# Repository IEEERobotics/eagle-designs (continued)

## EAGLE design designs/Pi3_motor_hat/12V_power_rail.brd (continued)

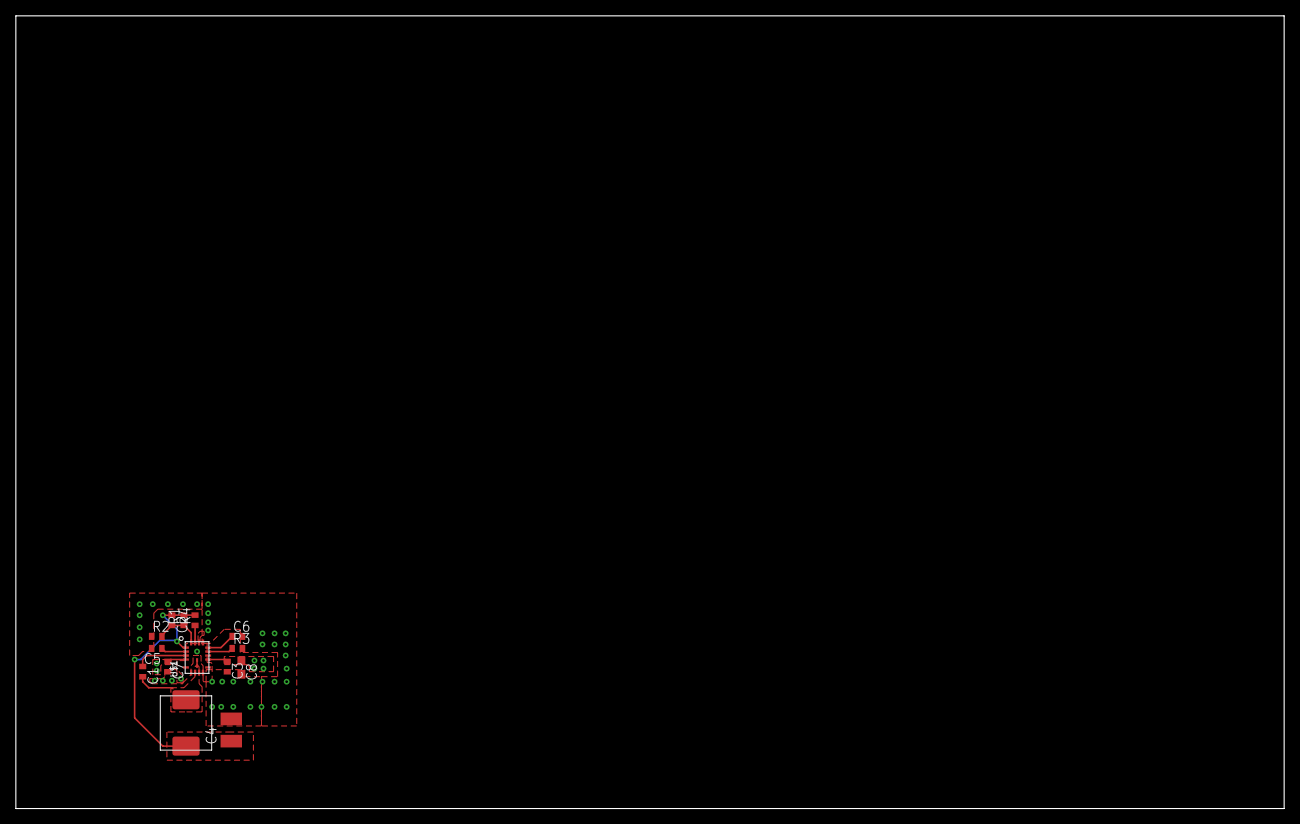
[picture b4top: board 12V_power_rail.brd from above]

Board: 2 copper layers, 160.0 x 100.0 mm, 14 parts (0 on the bottom side), 10 nets.

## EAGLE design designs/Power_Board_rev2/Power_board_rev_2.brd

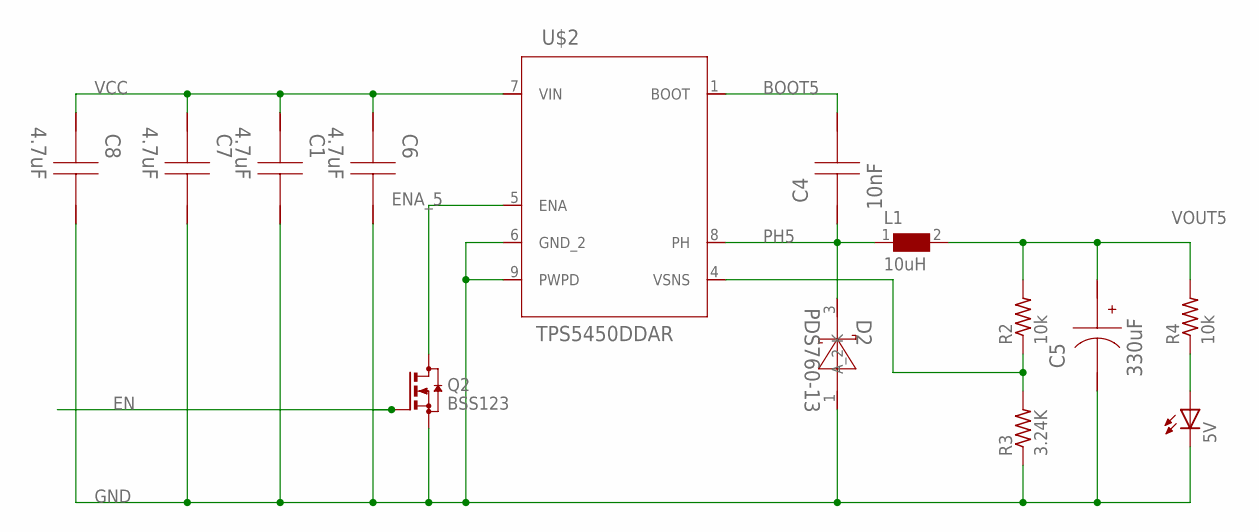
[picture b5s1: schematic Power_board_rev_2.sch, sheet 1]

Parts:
5V: LEDSML1206; SML1206
C1, C6, C7, C8: 4.7uF; 1206
C4: 10nF; 0805
C5: 330uF; SM_RADIAL_10AMM
D2: PDS760-13; POWERDI5
L1: 10uH; WE-HCC_1090
Q2: BSS123; SOT23
R2, R4: 10k; R1206
R3: 3.24K; R1206
U$2: TPS5450DDAR; R-PDSO-G8

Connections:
BOOT5: C4.1, U$2.1 (BOOT)
EN: Q2.1 (G); also elsewhere on the board
ENA_5: Q2.3 (D), U$2.5 (ENA)
FB5: 5V.A, R4.1
GND: 5V.C, C1.1, C5.2 (-), C6.1, C7.1, C8.1, D2.1 (A_2), Q2.2 (S), R3.1, U$2.6 (GND_2), U$2.9 (PWPD); also elsewhere on the board
PH5: C4.2, D2.3 (K), L1.1, U$2.8 (PH)
VCC: C1.2, C6.2, C7.2, C8.2, U$2.7 (VIN); also elsewhere on the board
VOUT5: C5.1 (+), L1.2, R2.2, R4.2; also elsewhere on the board
VSNS5: R2.1, R3.2, U$2.4 (VSNS)

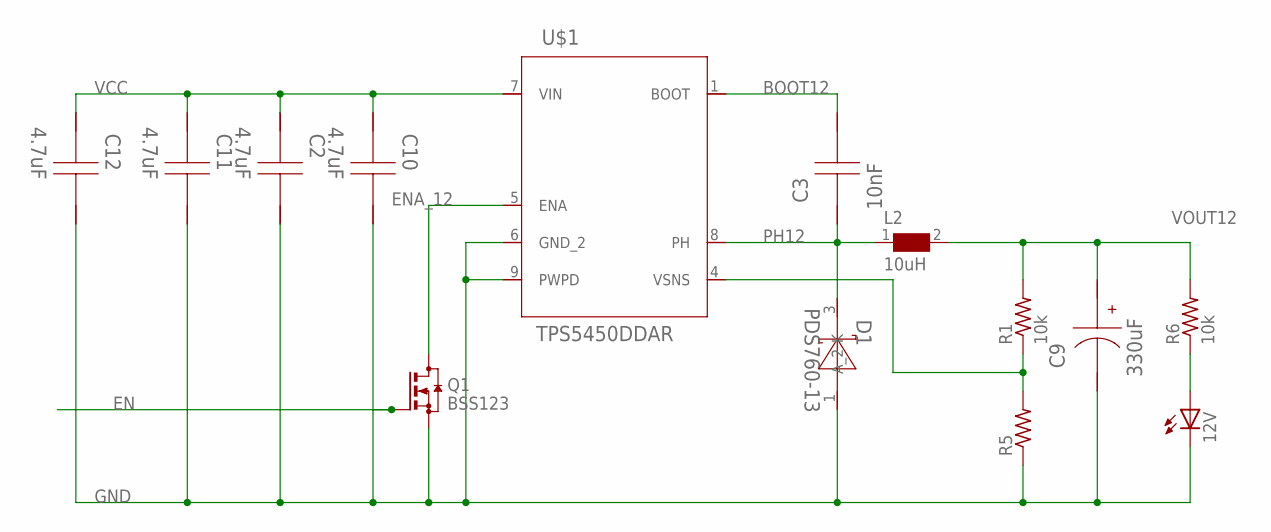
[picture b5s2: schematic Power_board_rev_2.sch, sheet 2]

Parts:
12V: LEDSML1206; SML1206
C2, C10, C11, C12: 4.7uF; 1206
C3: 10nF; 0805
C9: 330uF; SM_RADIAL_10AMM
D1: PDS760-13; POWERDI5
L2: 10uH; WE-HCC_1090
Q1: BSS123; SOT23
R1, R6: 10k; R1206
R5: R-US_R1206; R1206
U$1: TPS5450DDAR; R-PDSO-G8

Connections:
BOOT12: C3.1, U$1.1 (BOOT)
EN: Q1.1 (G); also elsewhere on the board
ENA_12: Q1.3 (D), U$1.5 (ENA)
FB12: 12V.A, R6.1
GND: 12V.C, C2.1, C9.2 (-), C10.1, C11.1, C12.1, D1.1 (A_2), Q1.2 (S), R5.1, U$1.6 (GND_2), U$1.9 (PWPD); also elsewhere on the board
PH12: C3.2, D1.3 (K), L2.1, U$1.8 (PH)
VCC: C2.2, C10.2, C11.2, C12.2, U$1.7 (VIN); also elsewhere on the board
VOUT12: C9.1 (+), L2.2, R1.2, R6.2; also elsewhere on the board
VSNS12: R1.1, R5.2, U$1.4 (VSNS)

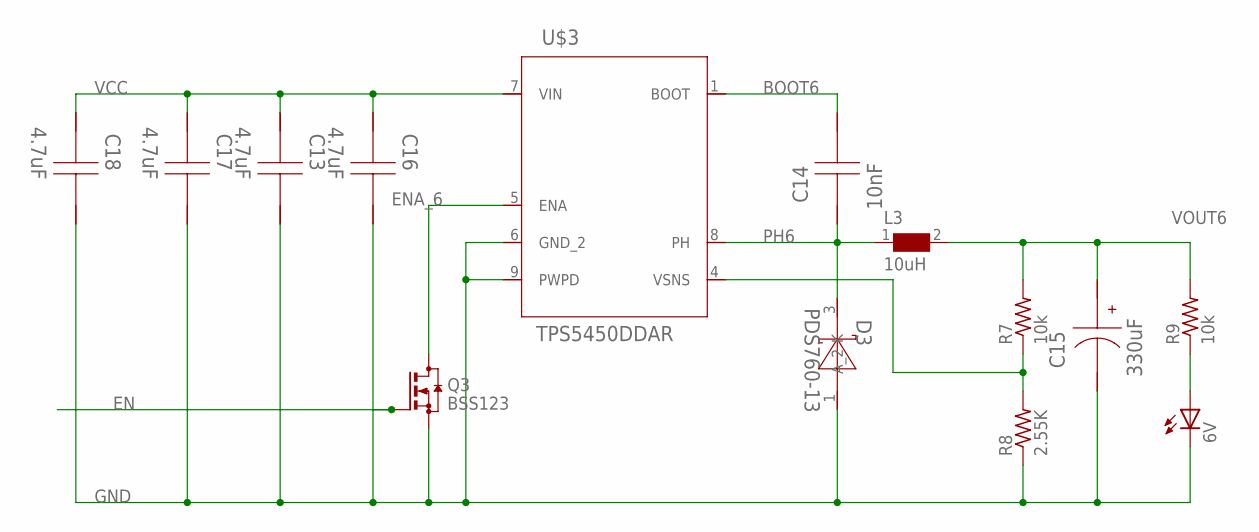
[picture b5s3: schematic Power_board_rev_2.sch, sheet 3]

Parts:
6V: LEDSML1206; SML1206
C13, C16, C17, C18: 4.7uF; 1206
C14: 10nF; 0805
C15: 330uF; SM_RADIAL_10AMM
D3: PDS760-13; POWERDI5
L3: 10uH; WE-HCC_1090
Q3: BSS123; SOT23
R7, R9: 10k; R1206
R8: 2.55K; R1206
U$3: TPS5450DDAR; R-PDSO-G8

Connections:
BOOT6: C14.1, U$3.1 (BOOT)
EN: Q3.1 (G); also elsewhere on the board
ENA_6: Q3.3 (D), U$3.5 (ENA)
FB6: 6V.A, R9.1
GND: 6V.C, C13.1, C15.2 (-), C16.1, C17.1, C18.1, D3.1 (A_2), Q3.2 (S), R8.1, U$3.6 (GND_2), U$3.9 (PWPD); also elsewhere on the board
PH6: C14.2, D3.3 (K), L3.1, U$3.8 (PH)
VCC: C13.2, C16.2, C17.2, C18.2, U$3.7 (VIN); also elsewhere on the board
VOUT6: C15.1 (+), L3.2, R7.2, R9.2; also elsewhere on the board
VSNS6: R7.1, R8.2, U$3.4 (VSNS)

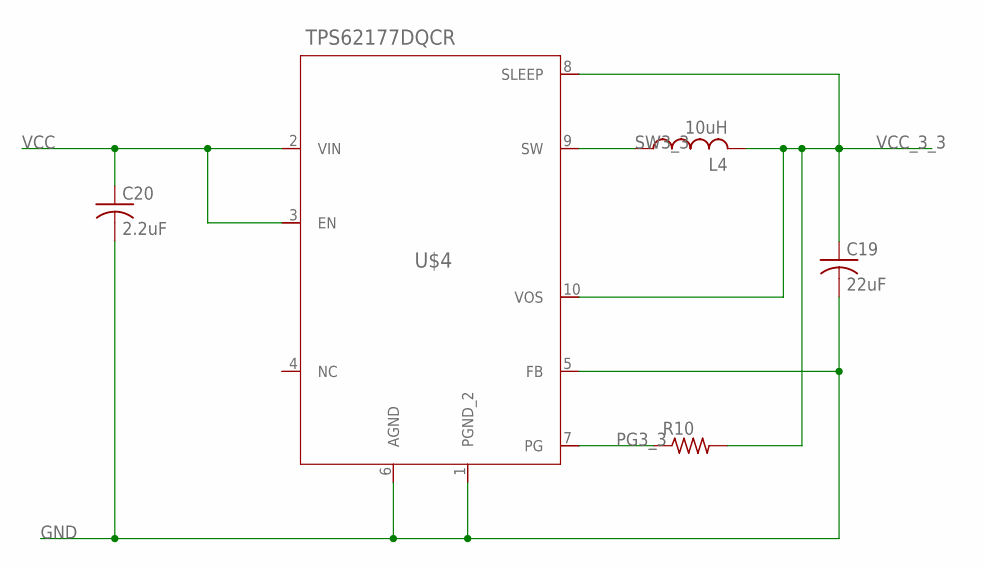
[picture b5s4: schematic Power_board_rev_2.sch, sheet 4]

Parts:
C19: 22uF; C0805
C20: 2.2uF; C1210K
L4: 10uH; POWER-CHOKE_WE-TPC
R10: R-US_R0402; R0402
U$4: TPS62177DQCR; R-PWSON-N10

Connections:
GND: C19.2, C20.2, U$4.1 (PGND_2), U$4.5 (FB), U$4.6 (AGND); also elsewhere on the board
PG3_3: R10.1, U$4.7 (PG)
SW3_3: L4.1, U$4.9 (SW)
VCC: C20.1, U$4.2 (VIN), U$4.3 (EN); also elsewhere on the board
VCC_3_3: C19.1, L4.2, R10.2, U$4.8 (SLEEP), U$4.10 (VOS); also elsewhere on the board

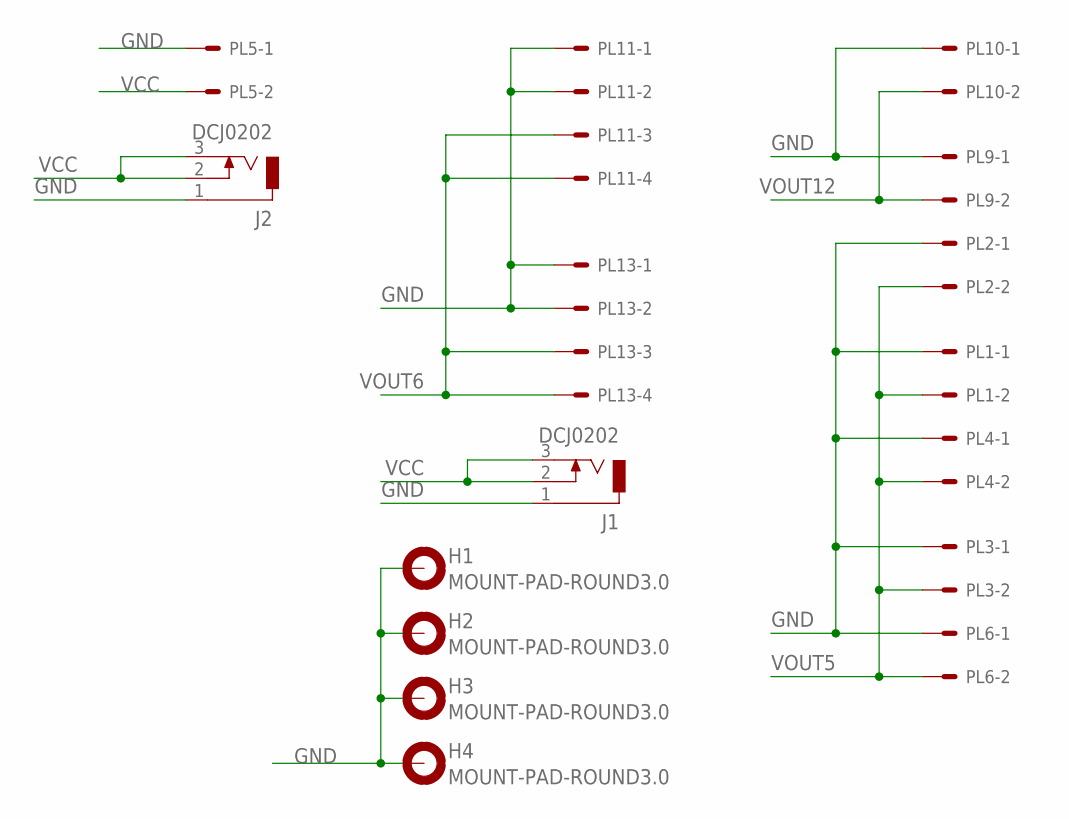
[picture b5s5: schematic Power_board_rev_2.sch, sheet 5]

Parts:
H1, H2, H3, H4: MOUNT-PAD-ROUND3.0; 3,0-PAD
J1, J2: DCJ0202
PL1, PL2, PL3, PL4, PL5, PL6, PL9, PL10: 555X-2H; 5569-2
PL11, PL13: 555X-4H; 5569-4

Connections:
GND: H1.B3,0, H2.B3,0, H3.B3,0, H4.B3,0, J1.1, J2.1, PL1.1, PL2.1, PL3.1, PL4.1, PL5.1, PL6.1, PL9.1, PL10.1, PL11.1, PL11.2, PL13.1, PL13.2; also elsewhere on the board
VCC: J1.2, J1.3, J2.2, J2.3, PL5.2; also elsewhere on the board
VOUT5: PL1.2, PL2.2, PL3.2, PL4.2, PL6.2; also elsewhere on the board
VOUT6: PL11.3, PL11.4, PL13.3, PL13.4; also elsewhere on the board
VOUT12: PL9.2, PL10.2; also elsewhere on the board

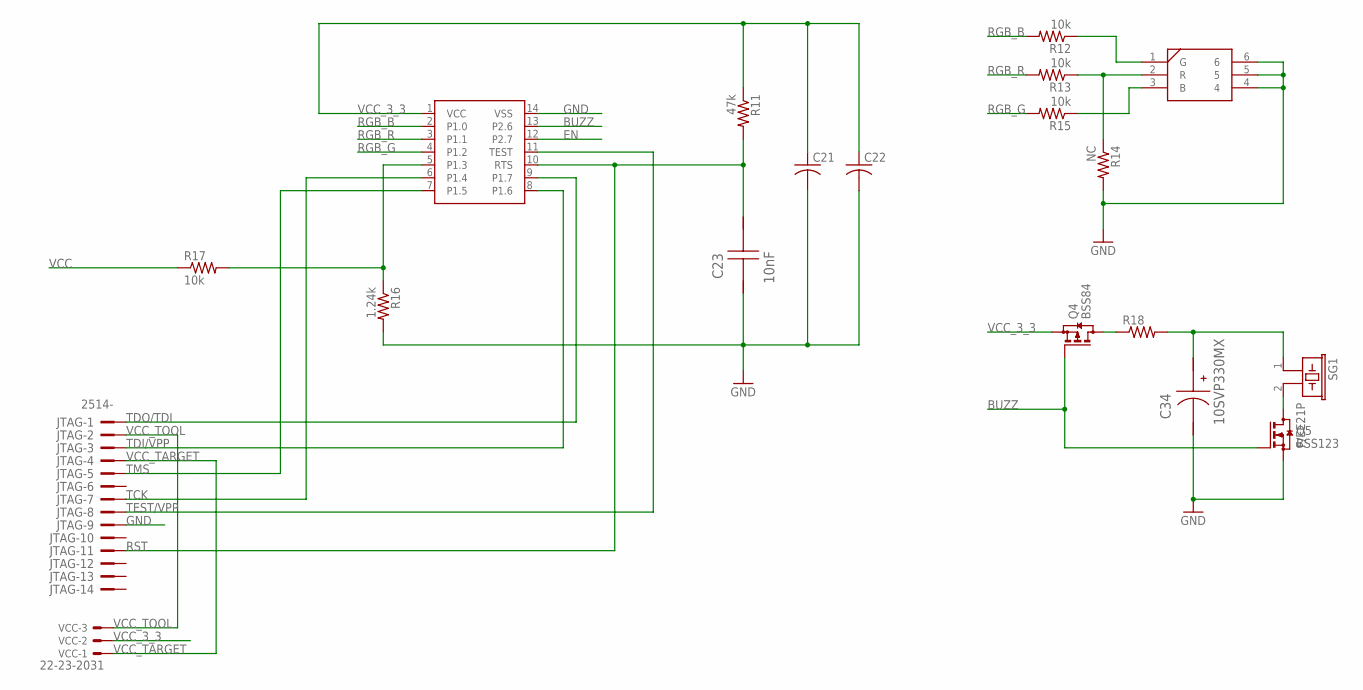
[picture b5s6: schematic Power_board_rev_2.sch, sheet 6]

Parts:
C21, C22: C-USC1206K; C1206K
C23: 10nF; 0805
C34: 10SVP330MX; SM_RADIAL_10AMM
JTAG: 2514-; PAK100/2500-14
Q4: BSS84; SOT23
Q5: BSS123; SOT23
R11: 47k; R1206W
R12, R13, R15, R17: 10k; R1206W
R14: NC; R1206W
R16: 1.24k; R1206W
R18: R-US_R1206W; R1206W
SG1: F/EE21P
U$5: MSP430F20X3; TSSOP-14
U$7: RGB; RGB_SMD
VCC: 22-23-2031

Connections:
BUZZ: Q4.1 (G), Q5.1 (G), U$5.13 (P2.6)
EN: U$5.12 (P2.7); also elsewhere on the board
GND: C21.2, C22.2, C23.2, C34.2 (-), JTAG.9, Q5.2 (S), R14.2, R16.2, U$5.14 (VSS), U$7.4, U$7.5, U$7.6; also elsewhere on the board
unnamed: Q5.3 (D), SG1.2
unnamed: R13.1, R14.1, U$7.2 (R)
unnamed: R15.1, U$7.3 (B)
unnamed: R12.1, U$7.1 (G)
unnamed: C34.1 (+), R18.2, SG1.1
unnamed: R16.1, R17.2, U$5.5 (P1.3)
unnamed: Q4.3 (D), R18.1
RGB_B: R12.2, U$5.2 (P1.0)
RGB_G: R15.2, U$5.4 (P1.2)
RGB_R: R13.2, U$5.3 (P1.1)
RST: C23.1, JTAG.11, R11.2, U$5.10 (RTS)
TCK: JTAG.7, U$5.6 (P1.4)
TDI/VPP: JTAG.3, U$5.8 (P1.6)
TDO/TDI: JTAG.1, U$5.9 (P1.7)
TEST/VPP: JTAG.8, U$5.11 (TEST)
TMS: JTAG.5, U$5.7 (P1.5)
VCC: R17.1; also elsewhere on the board
VCC_3_3: C21.1, C22.1, Q4.2 (S), R11.1, U$5.1 (VCC), VCC.2; also elsewhere on the board
VCC_TARGET: JTAG.4, VCC.1
VCC_TOOL: JTAG.2, VCC.3

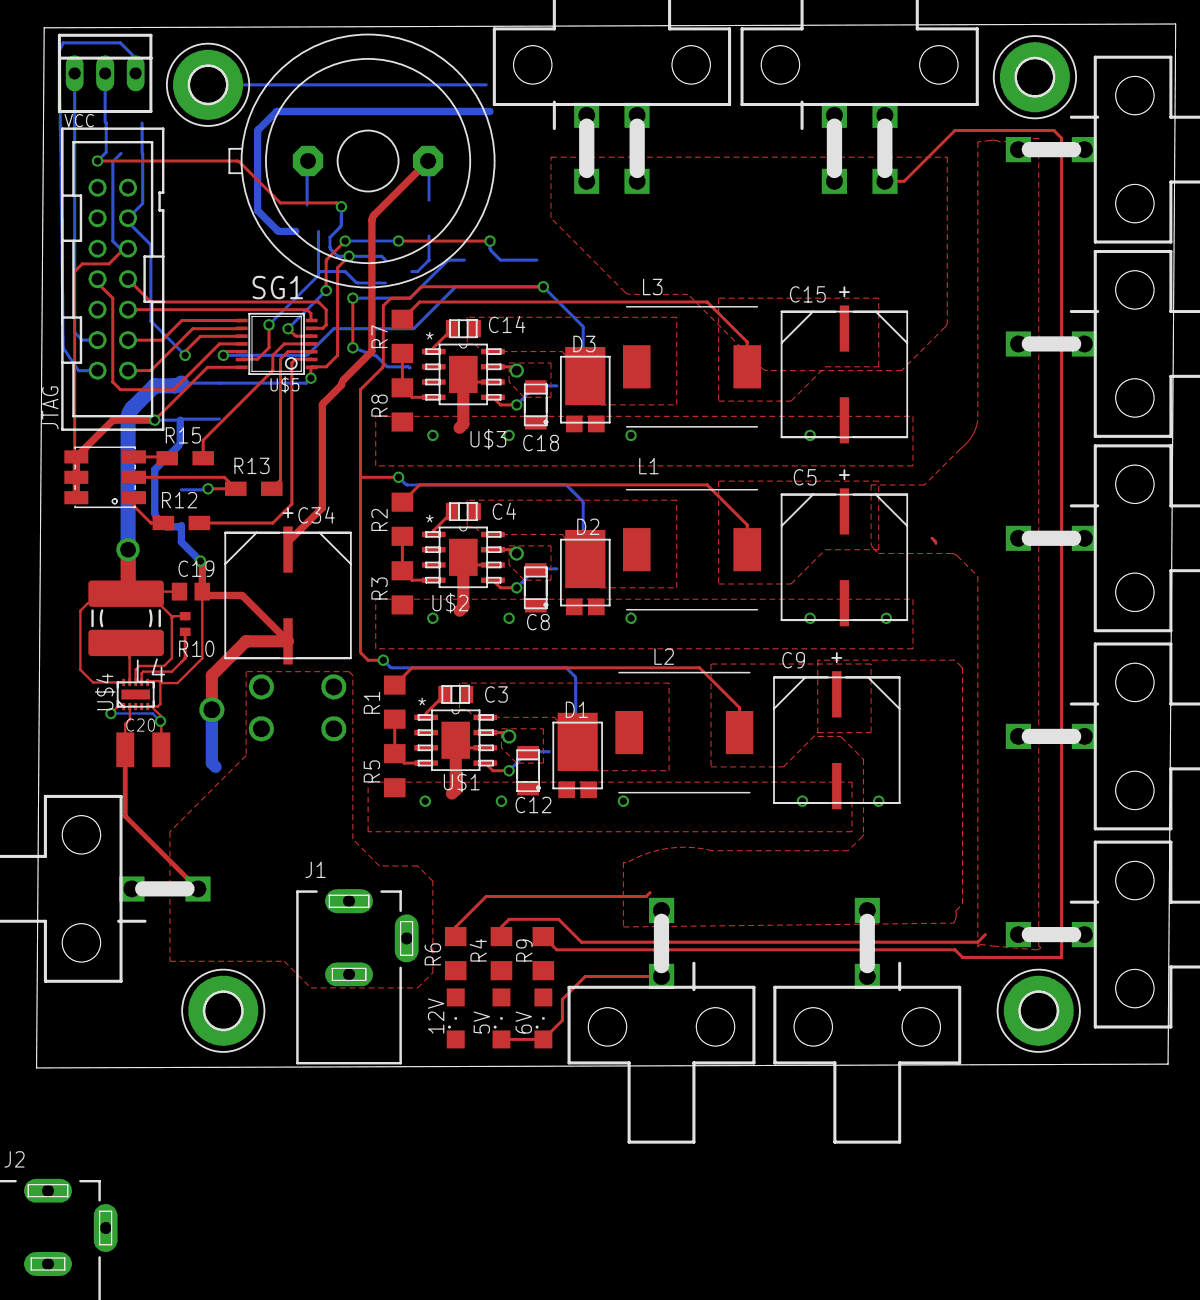
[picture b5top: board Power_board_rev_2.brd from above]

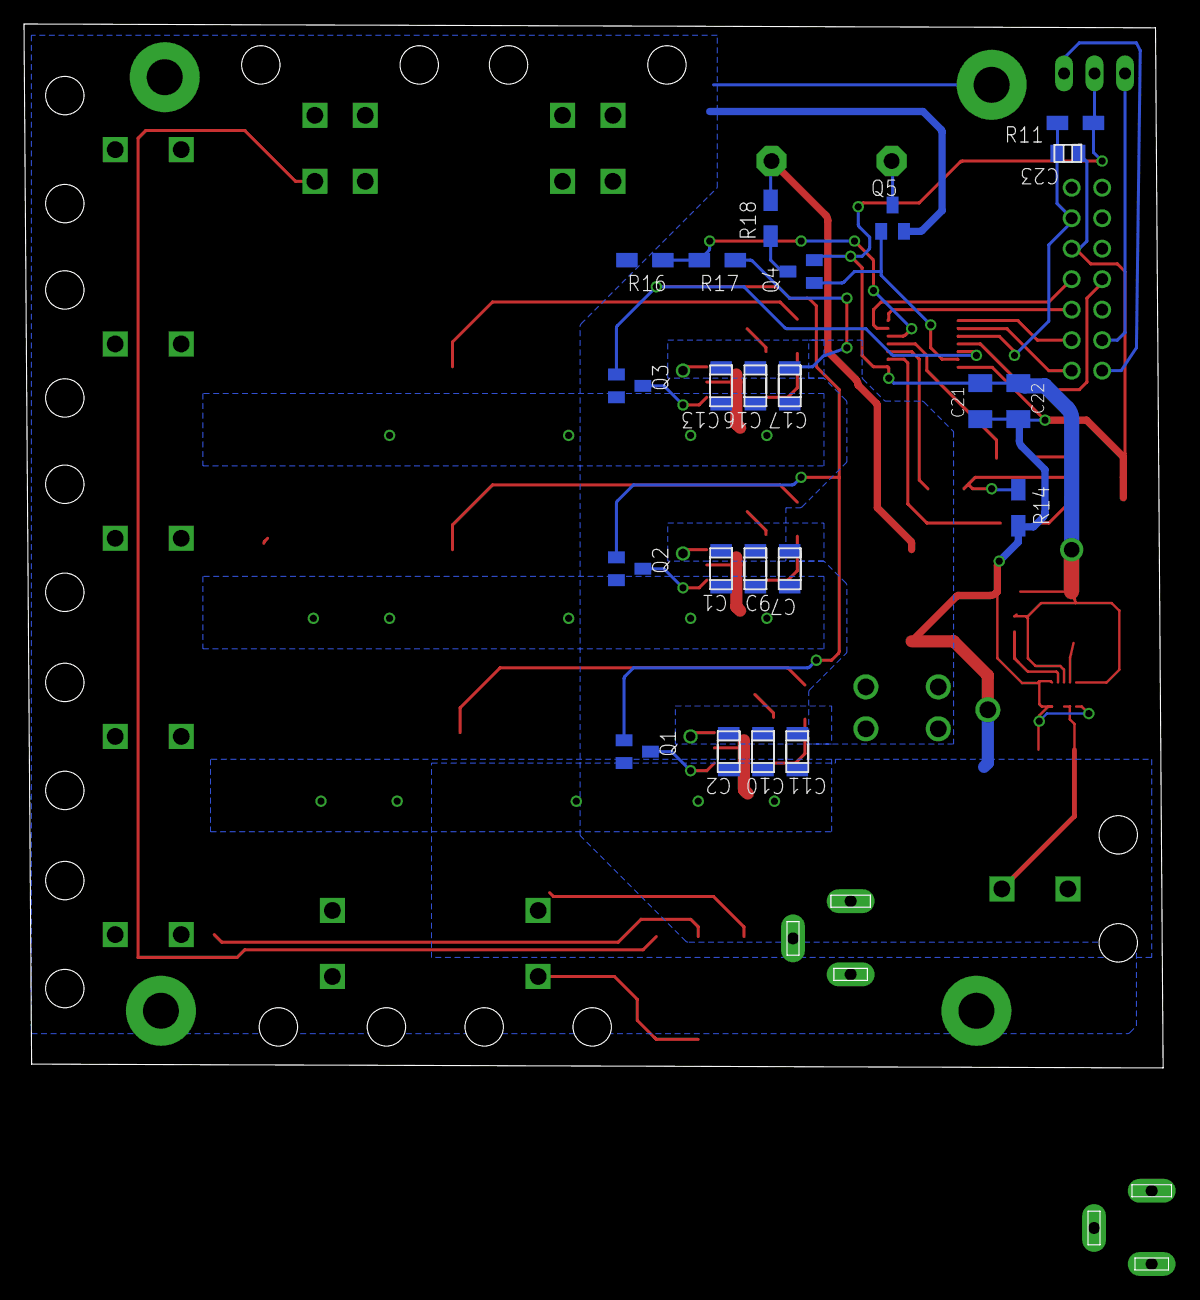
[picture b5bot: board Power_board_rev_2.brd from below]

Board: 2 copper layers, 94.9 x 87.0 mm, 82 parts (22 on the bottom side), 43 nets.

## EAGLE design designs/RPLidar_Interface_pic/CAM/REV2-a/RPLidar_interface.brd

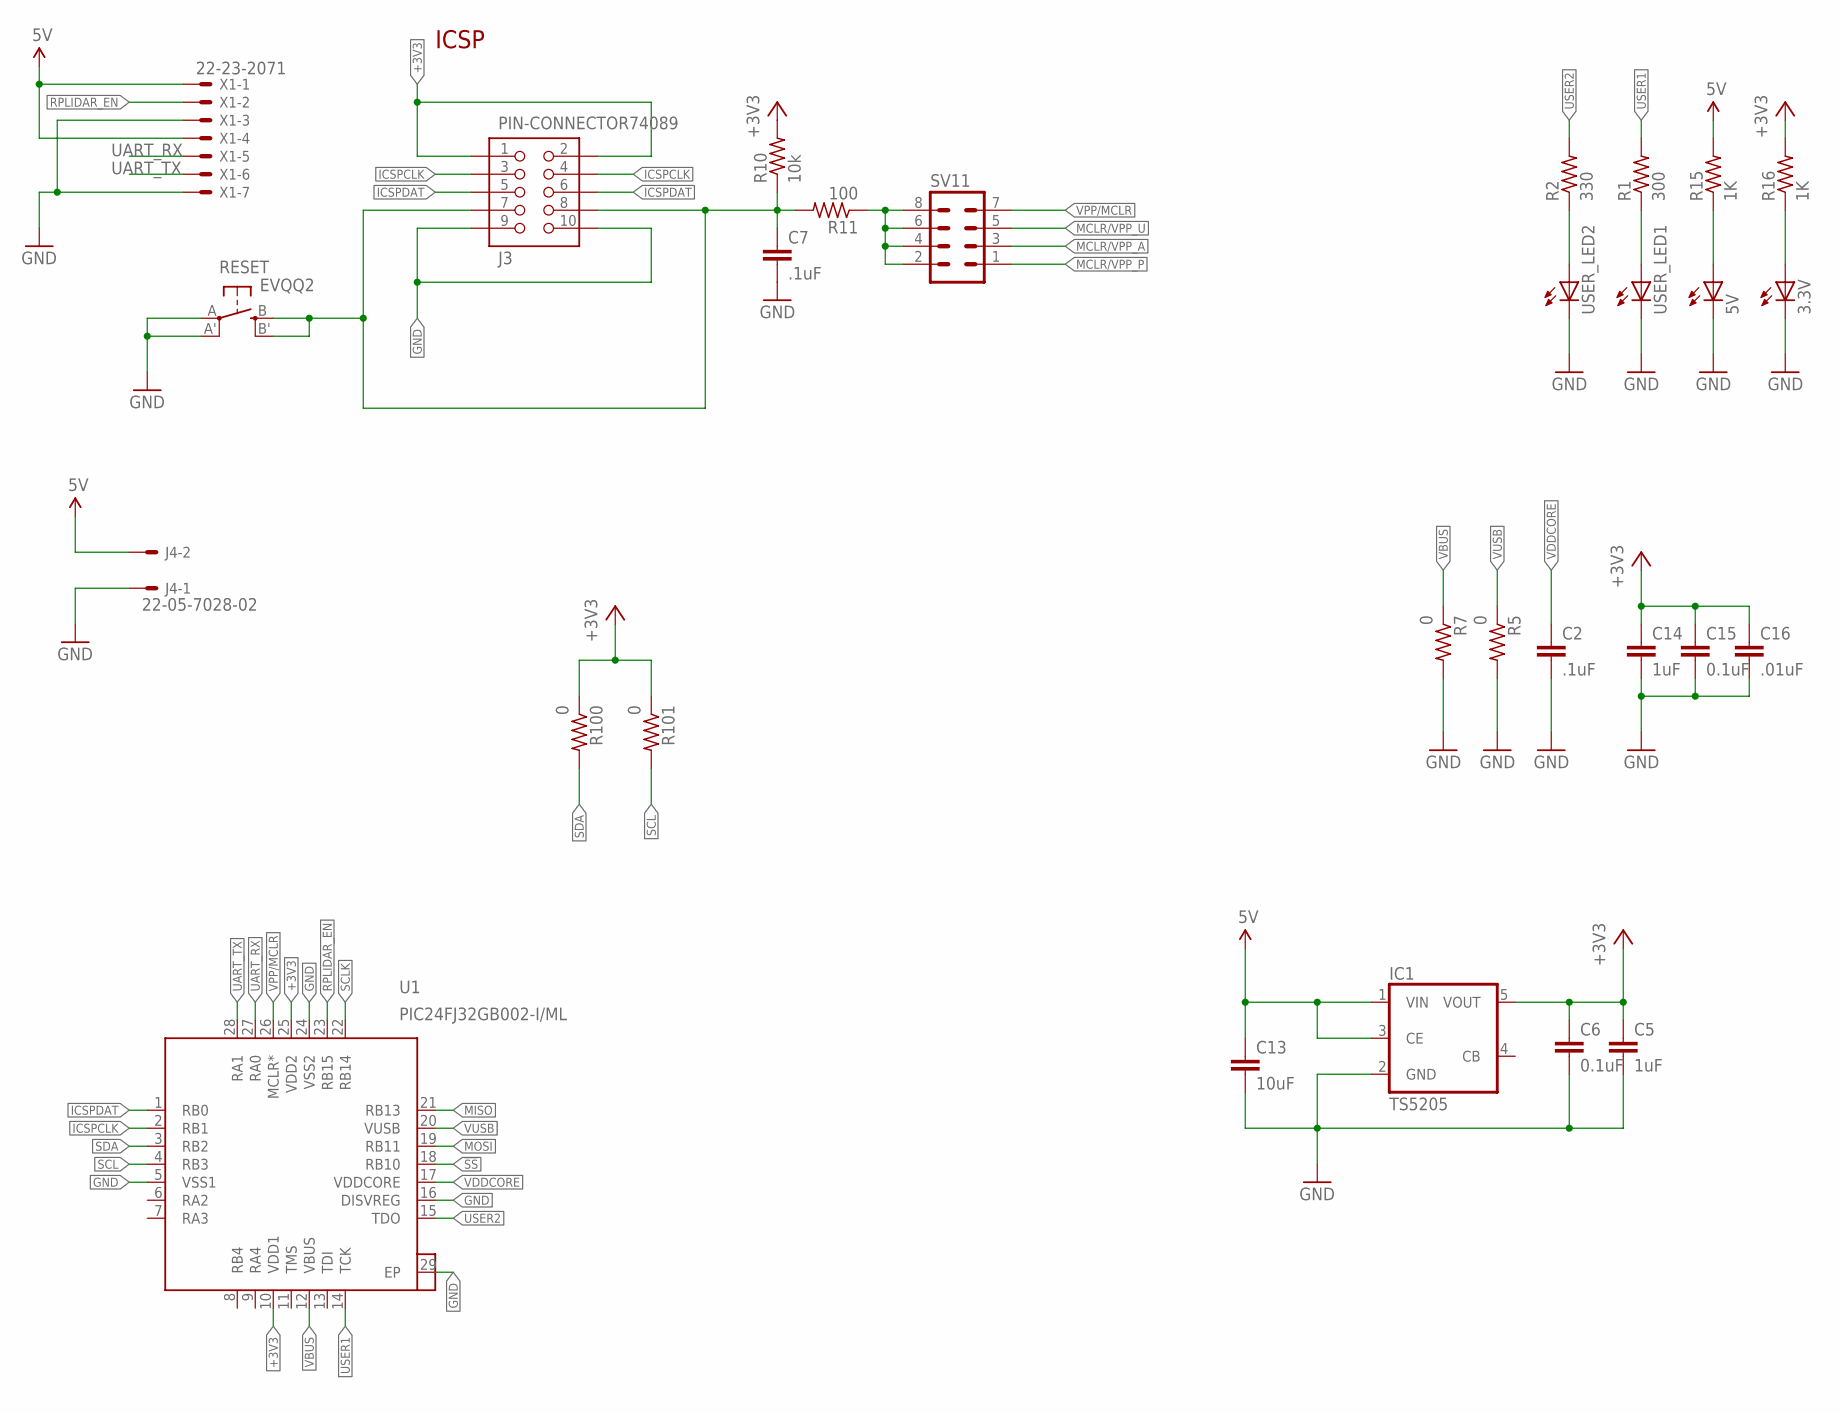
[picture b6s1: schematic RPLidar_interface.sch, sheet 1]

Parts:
3.3V, 5V: LEDCHIP-LED0603; CHIP-LED0603
C2, C7: .1uF; C0402
C5, C14: 1uF; C0402
C6, C15: 0.1uF; C0402
C13: 10uF; C0402
C16: .01uF; C0402
IC1: TS5205; SOT25
J3: PIN-CONNECTOR74089; 10-PIN-SMD
J4: 22-05-7028-02; 7395-02
R1: 300; R0402
R2: 330; R0402
R5, R7, R100, R101: 0; R0402
R10: 10k; R0402
R11: 100; R0402
R15, R16: 1K; R0402
RESET: EVQQ2; EVQ-Q2
SV11: MA04-2
U1: PIC24FJ32GB002-I/ML; QFN65P600X600X100-29N
USER_LED1, USER_LED2: LEDCHIP-LED0603; CHIP-LED0603
X1: 22-23-2071

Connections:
5V: C13.1, IC1.1 (VIN), IC1.3 (CE), J4.2, R15.2, X1.1, X1.4; also elsewhere on the board
!SS: U1.18 (RB10); also elsewhere on the board
+3V3: C5.1, C6.1, C14.1, C15.1, C16.1, IC1.5 (VOUT), J3.1, J3.2, R10.2, R16.2, R100.1, R101.1, U1.10 (VDD1), U1.25 (VDD2); also elsewhere on the board
GND: 3.3V.C, 5V.C, C2.2, C5.2, C6.2, C7.2, C13.2, C14.2, C15.2, C16.2, IC1.2 (GND), J3.9, J3.10, J4.1, R5.2, R7.2, RESET.A, RESET.A' (P1), U1.5 (VSS1), U1.16 (DISVREG), U1.24 (VSS2), U1.29 (EP), USER_LED1.C, USER_LED2.C, X1.3, X1.7; also elsewhere on the board
ICSPCLK: J3.3, J3.4, U1.2 (RB1); also elsewhere on the board
ICSPDAT: J3.5, J3.6, U1.1 (RB0); also elsewhere on the board
MCLR/VPP_A: SV11.3; also elsewhere on the board
MCLR/VPP_P: SV11.1; also elsewhere on the board
MCLR/VPP_U: SV11.5; also elsewhere on the board
MCLR_LIDAR: C7.1, J3.7, J3.8, R10.1, R11.2, RESET.B (S), RESET.B' (S1)
MISO: U1.21 (RB13); also elsewhere on the board
MOSI: U1.19 (RB11); also elsewhere on the board
unnamed: 3.3V.A, R16.1
unnamed: R1.1, USER_LED1.A
unnamed: R2.1, USER_LED2.A
unnamed: 5V.A, R15.1
unnamed: R11.1, SV11.2, SV11.4, SV11.6, SV11.8
RPLIDAR_EN: U1.23 (RB15), X1.2
SCL: R101.2, U1.4 (RB3); also elsewhere on the board
SCLK: U1.22 (RB14); also elsewhere on the board
SDA: R100.2, U1.3 (RB2); also elsewhere on the board
UART_RX: U1.27 (RA0), X1.5
UART_TX: U1.28 (RA1), X1.6
USER1: R1.2, U1.14 (TCK)
USER2: R2.2, U1.15 (TDO)
VBUS: R7.1, U1.12 (VBUS)
VDDCORE: C2.1, U1.17 (VDDCORE)
VPP/MCLR: SV11.7, U1.26 (MCLR*)
VUSB: R5.1, U1.20 (VUSB)

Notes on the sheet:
ICSP

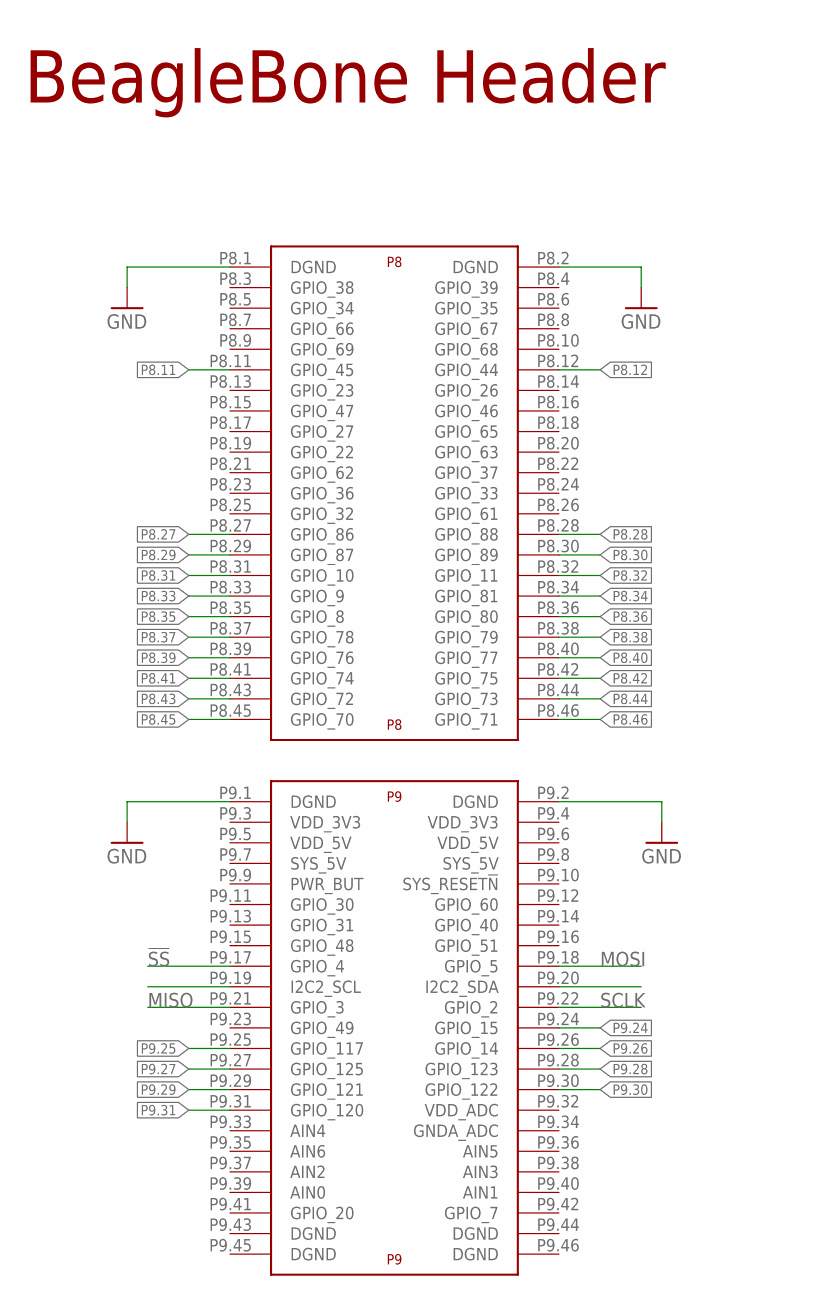
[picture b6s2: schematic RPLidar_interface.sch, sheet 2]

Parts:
U$3: BEAGLE_BONE_BLACK_CAPE

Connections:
!SS: U$3.P9.17 (GPIO_4); also elsewhere on the board
GND: U$3.P8.1 (DGND), U$3.P8.2 (DGND), U$3.P9.1 (DGND), U$3.P9.2 (DGND); also elsewhere on the board
MISO: U$3.P9.21 (GPIO_3); also elsewhere on the board
MOSI: U$3.P9.18 (GPIO_5); also elsewhere on the board
P8.11: U$3.P8.11 (GPIO_45); also elsewhere on the board
P8.12: U$3.P8.12 (GPIO_44); also elsewhere on the board
P8.27: U$3.P8.27 (GPIO_86); also elsewhere on the board
P8.28: U$3.P8.28 (GPIO_88); also elsewhere on the board
P8.29: U$3.P8.29 (GPIO_87); also elsewhere on the board
P8.30: U$3.P8.30 (GPIO_89); also elsewhere on the board
P8.31: U$3.P8.31 (GPIO_10); also elsewhere on the board
P8.32: U$3.P8.32 (GPIO_11); also elsewhere on the board
P8.33: U$3.P8.33 (GPIO_9); also elsewhere on the board
P8.34: U$3.P8.34 (GPIO_81); also elsewhere on the board
P8.35: U$3.P8.35 (GPIO_8); also elsewhere on the board
P8.36: U$3.P8.36 (GPIO_80); also elsewhere on the board
P8.37: U$3.P8.37 (GPIO_78); also elsewhere on the board
P8.38: U$3.P8.38 (GPIO_79); also elsewhere on the board
P8.39: U$3.P8.39 (GPIO_76); also elsewhere on the board
P8.40: U$3.P8.40 (GPIO_77); also elsewhere on the board
P8.41: U$3.P8.41 (GPIO_74); also elsewhere on the board
P8.42: U$3.P8.42 (GPIO_75); also elsewhere on the board
P8.43: U$3.P8.43 (GPIO_72); also elsewhere on the board
P8.44: U$3.P8.44 (GPIO_73); also elsewhere on the board
P8.45: U$3.P8.45 (GPIO_70); also elsewhere on the board
P8.46: U$3.P8.46 (GPIO_71); also elsewhere on the board
P9.24: U$3.P9.24 (GPIO_15)
P9.25: U$3.P9.25 (GPIO_117); also elsewhere on the board
P9.26: U$3.P9.26 (GPIO_14)
P9.27: U$3.P9.27 (GPIO_125); also elsewhere on the board
P9.28: U$3.P9.28 (GPIO_123); also elsewhere on the board
P9.29: U$3.P9.29 (GPIO_121); also elsewhere on the board
P9.30: U$3.P9.30 (GPIO_122); also elsewhere on the board
P9.31: U$3.P9.31 (GPIO_120); also elsewhere on the board
SCL: U$3.P9.19 (I2C2_SCL); also elsewhere on the board
SCLK: U$3.P9.22 (GPIO_2); also elsewhere on the board
SDA: U$3.P9.20 (I2C2_SDA); also elsewhere on the board

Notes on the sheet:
BeagleBone Header

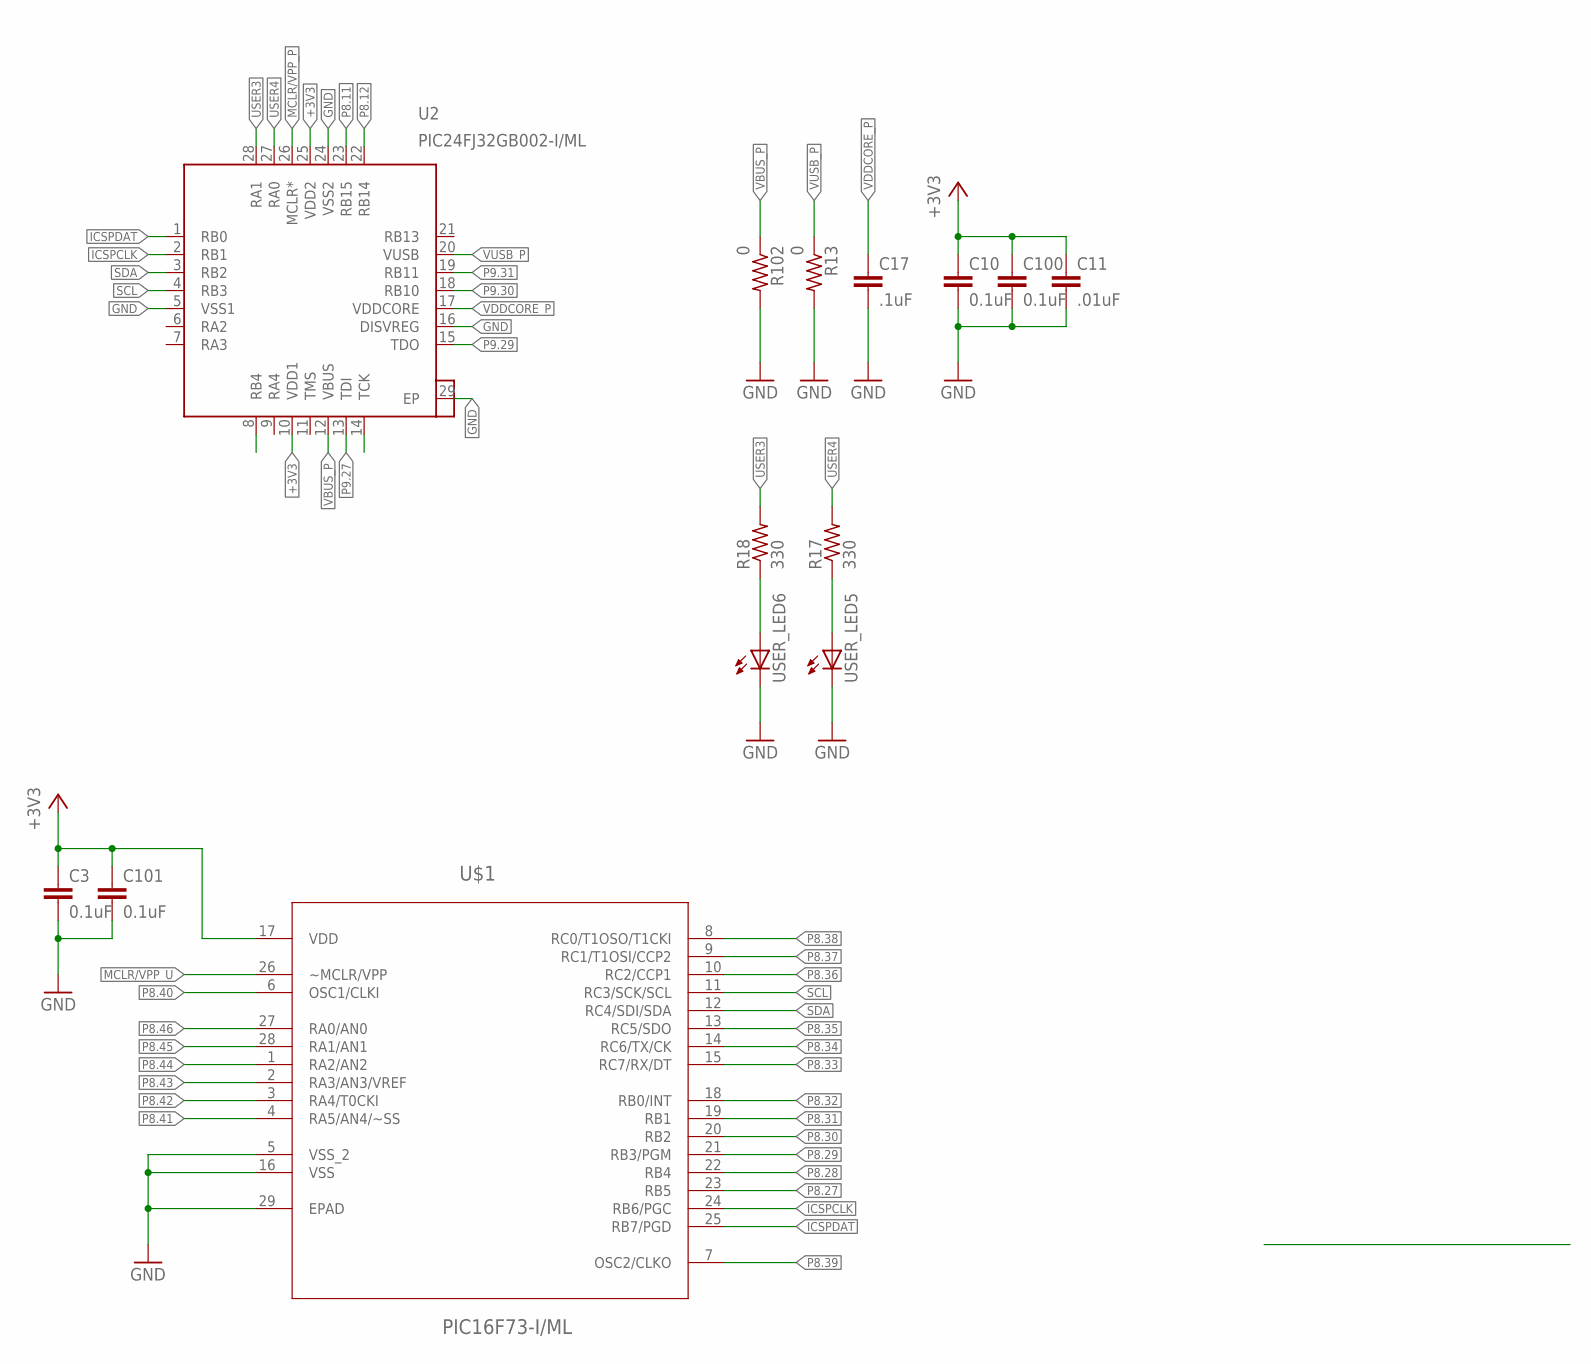
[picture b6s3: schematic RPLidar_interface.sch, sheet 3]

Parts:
C3, C10, C100, C101: 0.1uF; C0402
C11: .01uF; C0402
C17: .1uF; C0402
R13, R102: 0; R0402
R17, R18: 330; R0402
U2: PIC24FJ32GB002-I/ML; QFN65P600X600X100-29N
U$1: PIC16F73-I/ML; QFN65P600X600X100-28N
USER_LED5, USER_LED6: LEDCHIP-LED0603; CHIP-LED0603

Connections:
+3V3: C3.1, C10.1, C11.1, C100.1, C101.1, U2.10 (VDD1), U2.25 (VDD2), U$1.17 (VDD); also elsewhere on the board
GND: C3.2, C10.2, C11.2, C17.2, C100.2, C101.2, R13.2, R102.2, U2.5 (VSS1), U2.16 (DISVREG), U2.24 (VSS2), U2.29 (EP), U$1.5 (VSS_2), U$1.16 (VSS), U$1.29 (EPAD), USER_LED5.C, USER_LED6.C; also elsewhere on the board
ICSPCLK: U2.2 (RB1), U$1.24 (RB6/PGC); also elsewhere on the board
ICSPDAT: U2.1 (RB0), U$1.25 (RB7/PGD); also elsewhere on the board
MCLR/VPP_P: U2.26 (MCLR*); also elsewhere on the board
MCLR/VPP_U: U$1.26 (~MCLR/VPP); also elsewhere on the board
unnamed: R17.1, USER_LED5.A
unnamed: R18.1, USER_LED6.A
P8.11: U2.23 (RB15); also elsewhere on the board
P8.12: U2.22 (RB14); also elsewhere on the board
P8.27: U$1.23 (RB5); also elsewhere on the board
P8.28: U$1.22 (RB4); also elsewhere on the board
P8.29: U$1.21 (RB3/PGM); also elsewhere on the board
P8.30: U$1.20 (RB2); also elsewhere on the board
P8.31: U$1.19 (RB1); also elsewhere on the board
P8.32: U$1.18 (RB0/INT); also elsewhere on the board
P8.33: U$1.15 (RC7/RX/DT); also elsewhere on the board
P8.34: U$1.14 (RC6/TX/CK); also elsewhere on the board
P8.35: U$1.13 (RC5/SDO); also elsewhere on the board
P8.36: U$1.10 (RC2/CCP1); also elsewhere on the board
P8.37: U$1.9 (RC1/T1OSI/CCP2); also elsewhere on the board
P8.38: U$1.8 (RC0/T1OSO/T1CKI); also elsewhere on the board
P8.39: U$1.7 (OSC2/CLKO); also elsewhere on the board
P8.40: U$1.6 (OSC1/CLKI); also elsewhere on the board
P8.41: U$1.4 (RA5/AN4/~SS); also elsewhere on the board
P8.42: U$1.3 (RA4/T0CKI); also elsewhere on the board
P8.43: U$1.2 (RA3/AN3/VREF); also elsewhere on the board
P8.44: U$1.1 (RA2/AN2); also elsewhere on the board
P8.45: U$1.28 (RA1/AN1); also elsewhere on the board
P8.46: U$1.27 (RA0/AN0); also elsewhere on the board
P9.25: U2.8 (RB4); also elsewhere on the board
P9.27: U2.13 (TDI); also elsewhere on the board
P9.28: U2.14 (TCK); also elsewhere on the board
P9.29: U2.15 (TDO); also elsewhere on the board
P9.30: U2.18 (RB10); also elsewhere on the board
P9.31: U2.19 (RB11); also elsewhere on the board
SCL: U2.4 (RB3), U$1.11 (RC3/SCK/SCL); also elsewhere on the board
SDA: U2.3 (RB2), U$1.12 (RC4/SDI/SDA); also elsewhere on the board
USER3: R18.2, U2.28 (RA1)
USER4: R17.2, U2.27 (RA0)
VBUS_P: R102.1, U2.12 (VBUS)
VDDCORE_P: C17.1, U2.17 (VDDCORE)
VUSB_P: R13.1, U2.20 (VUSB)
